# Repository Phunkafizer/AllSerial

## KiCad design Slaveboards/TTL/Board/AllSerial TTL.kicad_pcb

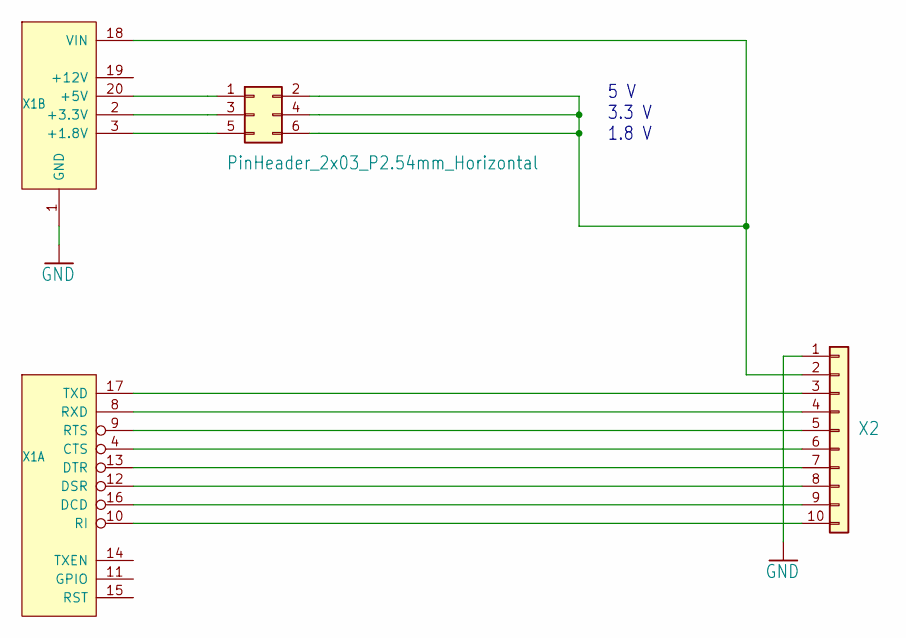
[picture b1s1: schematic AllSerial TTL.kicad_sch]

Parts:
X1: ALLSERIALSLAVE; SlaveBoard
X2: AKL18X-10W; Metz_PT11310HBBN_182
X3: PinHeader_2x03_P2.54mm_Horizontal

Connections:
GND: X1.1 (GND), X2.1
unnamed: X1.4 (CTS), X2.6
unnamed: X1.16 (DCD), X2.9
unnamed: X1.12 (DSR), X2.8
unnamed: X1.13 (DTR), X2.7
unnamed: X1.10 (RI), X2.10
unnamed: X1.9 (RTS), X2.5
unnamed: X1.8 (RXD), X2.4
unnamed: X1.17 (TXD), X2.3
unnamed: X1.3 (+1.8V), X3.5
unnamed: X1.2 (+3.3V), X3.3
unnamed: X1.20 (+5V), X3.1
unnamed: X1.18 (VIN), X2.2, X3.2, X3.4, X3.6

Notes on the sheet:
5 V 3.3 V 1.8 V

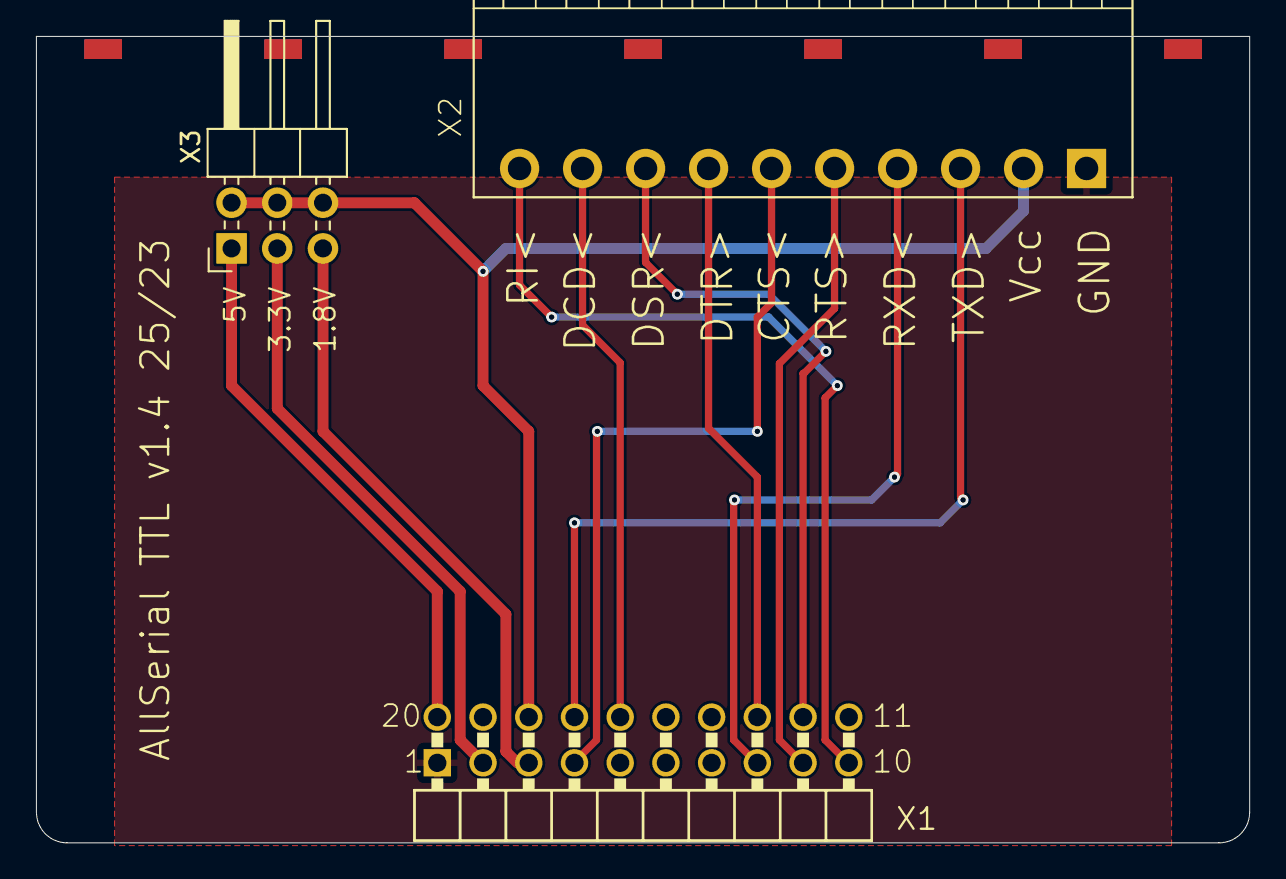
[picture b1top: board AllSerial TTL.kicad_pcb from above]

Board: 2 copper layers, 67.4 x 44.8 mm, 3 parts (0 on the bottom side), 13 nets.

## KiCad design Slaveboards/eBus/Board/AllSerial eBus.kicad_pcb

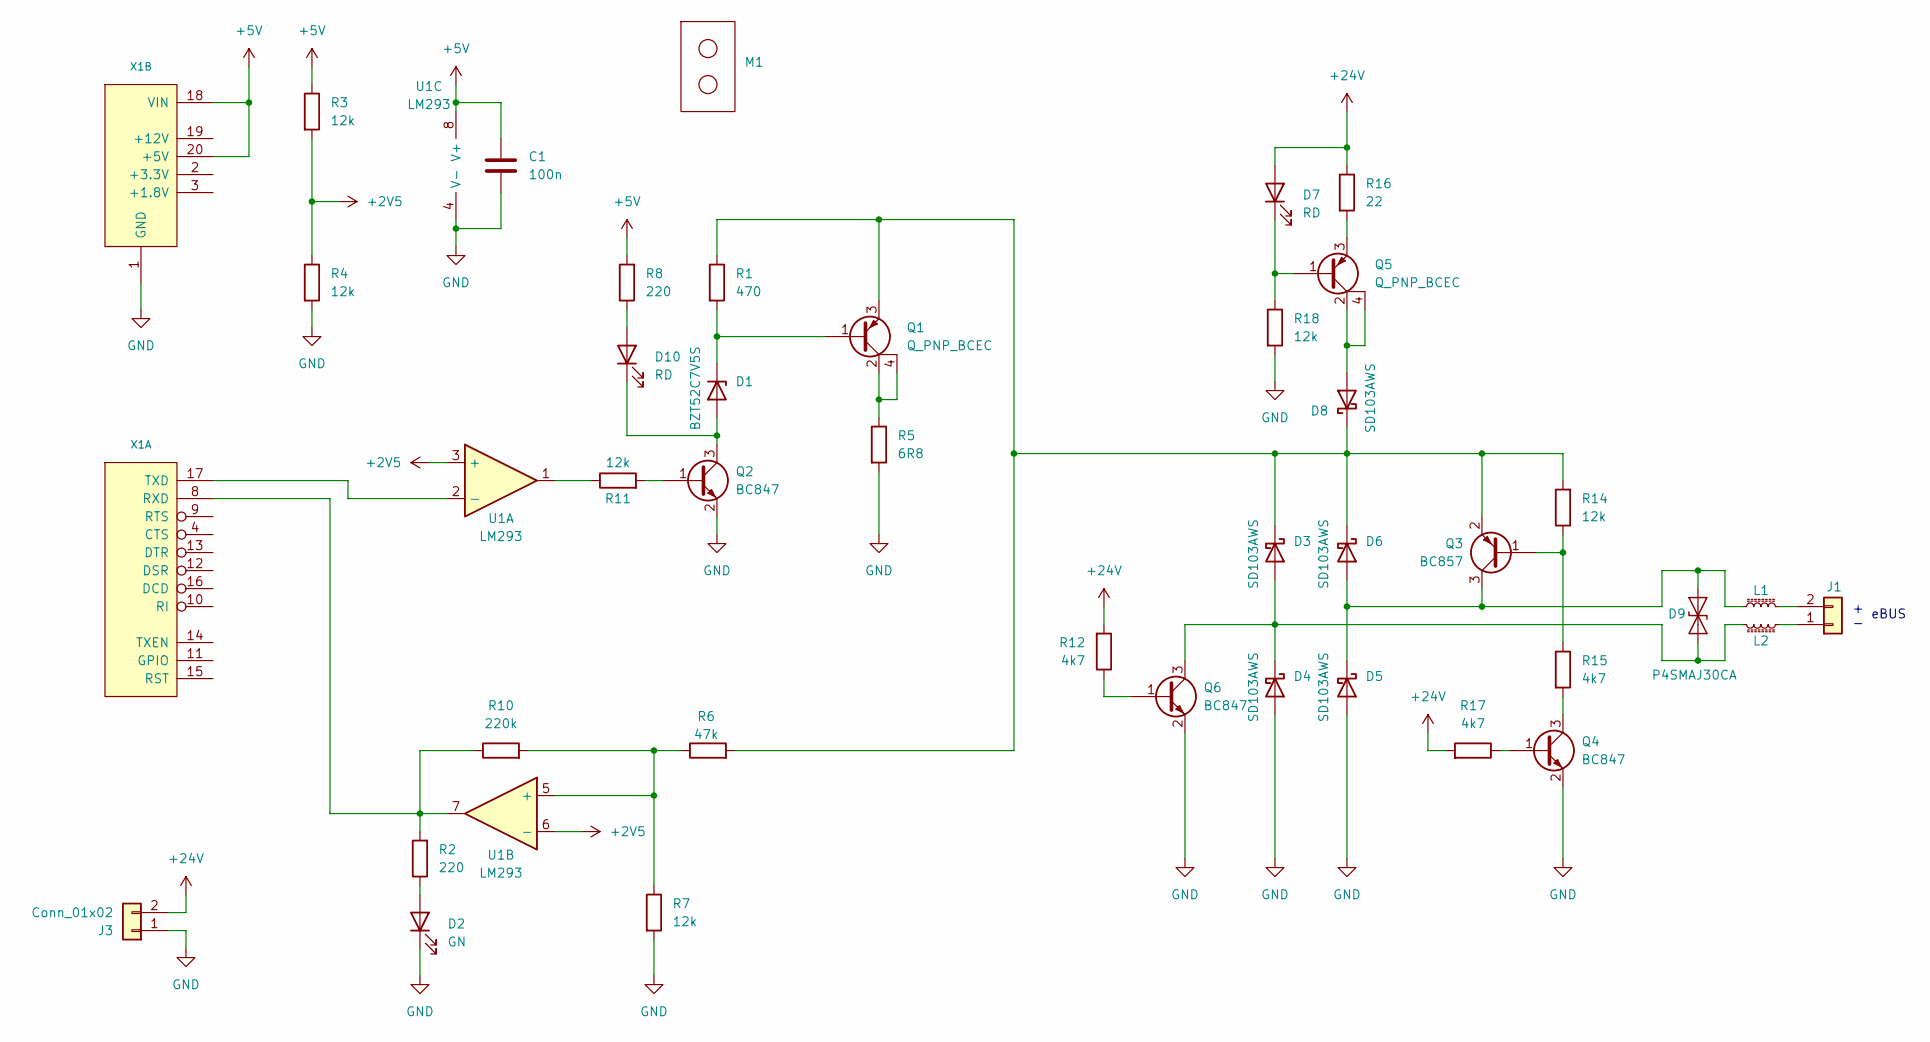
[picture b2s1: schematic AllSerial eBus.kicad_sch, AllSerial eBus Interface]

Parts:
C1: 100n; C_0805_2012Metric
D1: BZT52C7V5S; D_SOD-123
D2: GN; LED_0603_1608Metric
D3, D4, D5, D6, D8: SD103AWS; D_SOD-323
D7, D10: RD; LED_0603_1608Metric
D9: P4SMAJ30CA; D_SMA
J1: Metz_PT11302HBBN_182
J3: Conn_01x02; Metz_PT11302HBBN_182
L1, L2: L_0805_2012Metric
M1: Mentor 1296.2012
Q1, Q5: Q_PNP_BCEC; SOT-223
Q2, Q4, Q6: BC847; SOT-23
Q3: BC857; SOT-23
R1: 470; R_0805_2012Metric
R2, R8: 220; R_0805_2012Metric
R3, R4, R7, R11, R14, R18: 12k; R_0805_2012Metric
R5: 6R8; R_0805_2012Metric
R6: 47k; R_0805_2012Metric
R10: 220k; R_0805_2012Metric
R12, R15, R17: 4k7; R_0805_2012Metric
R16: 22; R_0805_2012Metric
U1: LM293; SO-8_3.9x4.9mm_P1.27mm
X1: AllSerial_Connector; SlaveBoard

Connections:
+2V5: R3.2, R4.1, U1.3 (+), U1.6 (-)
+5V: C1.1, R3.1, R8.2, U1.8 (V+), X1.18 (VIN), X1.20 (+5V)
+24V: D7.2 (A), J3.2, R12.2, R16.1, R17.2
GND: C1.2, D2.1 (K), D4.2 (A), D5.2 (A), J3.1, Q2.2 (E), Q4.2 (E), Q6.2 (E), R4.2, R5.2, R7.2, R18.2, U1.4 (V-), X1.1 (GND)
unnamed: D1.2 (A), D10.1 (K), Q2.3 (C)
unnamed: D1.1 (K), Q1.1 (B), R1.2
unnamed: D2.2 (A), R2.1
unnamed: D3.2 (A), D4.1 (K), D9.1 (A1), L2.2, Q6.3 (C)
unnamed: D3.1 (K), D6.1 (K), D8.1 (K), Q1.3 (E), Q3.2 (E), R1.1, R6.2, R14.2
unnamed: D5.1 (K), D6.2 (A), D9.2 (A2), L1.1, Q3.3 (C)
unnamed: D7.1 (K), Q5.1 (B), R18.1
unnamed: D8.2 (A), Q5.2 (C), Q5.4 (C)
unnamed: D10.2 (A), R8.1
unnamed: J1.1, L2.1
unnamed: J1.2, L1.2
unnamed: Q1.2 (C), Q1.4 (C), R5.1
unnamed: Q2.1 (B), R11.2
unnamed: Q3.1 (B), R14.1, R15.1
unnamed: Q4.1 (B), R17.1
unnamed: Q4.3 (C), R15.2
unnamed: Q5.3 (E), R16.2
unnamed: Q6.1 (B), R12.1
unnamed: R11.1, U1.1
unnamed: U1.2 (-), X1.17 (TXD)
unnamed: R6.1, R7.1, R10.2, U1.5 (+)
unnamed: R2.2, R10.1, U1.7, X1.8 (RXD)

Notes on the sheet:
+ -
eBUS

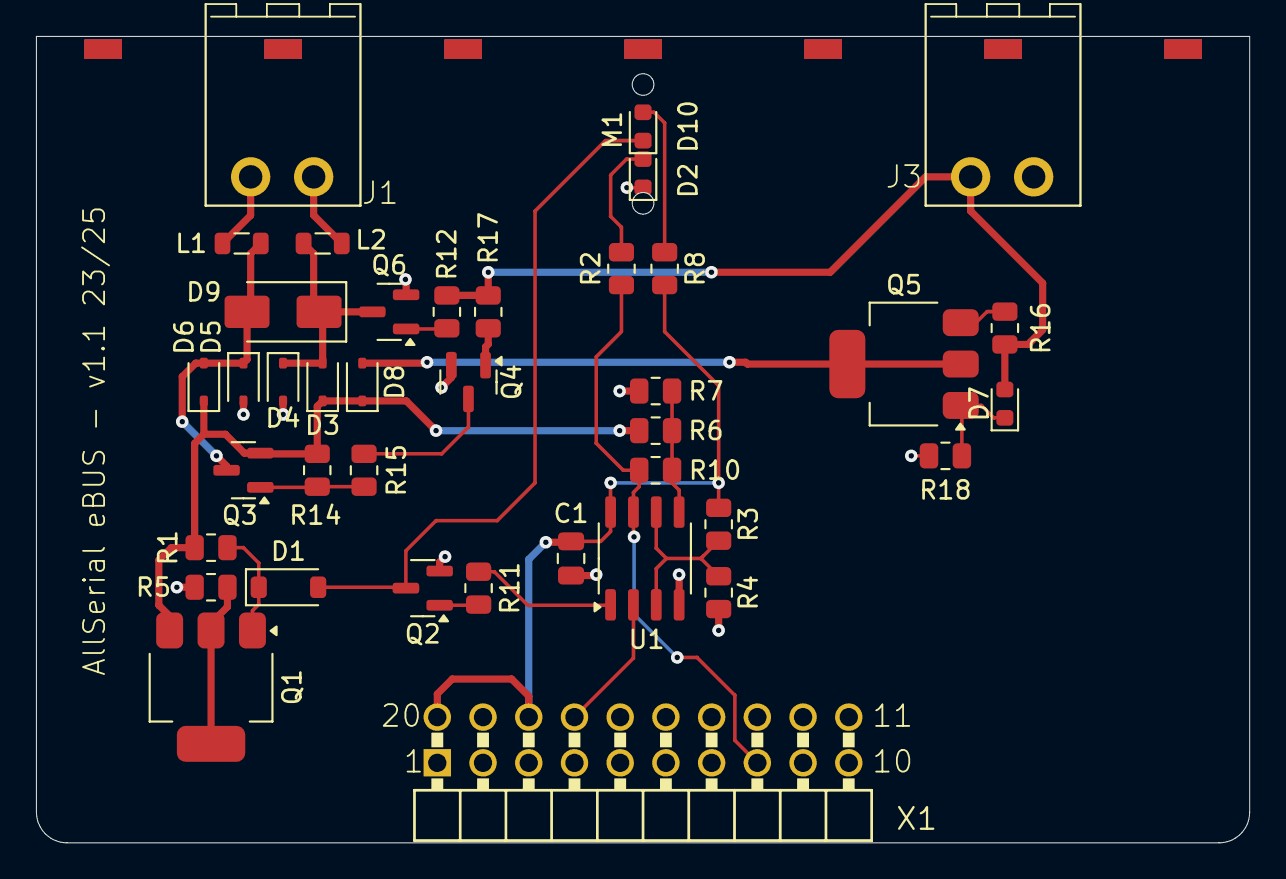
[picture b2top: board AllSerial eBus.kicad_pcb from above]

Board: 2 copper layers, 67.4 x 44.8 mm, 40 parts (0 on the bottom side), 26 nets.
